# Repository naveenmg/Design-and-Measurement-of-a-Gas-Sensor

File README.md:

# Design and Measurement of a Gas Sensor

### Task

The aim of this project is to develop a semiconductor gas sensor to measure the concentration of methane. Metal oxide sensors are also known as chemiresistors. The detection principle of resistive sensors is based on the change of resistance of a thin film upon adsorption of the gas molecules on the surface of a semiconductor. The gas-solid interactions affect the resistance of the film because of the density of electronic species in the film.

Two substrates consisting of aluminum oxide (Al2O3) are given for this project. The development processes will be explained in the following chapters. It includes sputtering, design of the electrode structure, laser structuring, microscopy, design and layout of a printed circuit board (PCB), soldering and testing.

## Structure of the gas sensor

In order to be able to apply the principle of operation a pattern of conductors has to be created between two contact surfaces. These surfaces as well as the conductors consist of a thin layer of platinum which itself is on top of a non-conductive substrate. Above the platinum pattern there is a layer of tin oxide, but at the contacting surfaces the platinum is still exposed. In order to make the effect (change in resistance) easier to measure, the surface area of the pattern should be as high as possible. This is achieved by having small distances between the conductors in the pattern. Since the effect occurs mainly in the space charge zone, the reaction material should be applied only in a thin layer.

To implement the design of the electrodes, the Easily Applicable Graphical Layout Editor (EAGLE) was used. This software is suitable for creating schematics and layouts for board designs, but also includes other features.

## Sputtering
Sputtering is one possibility of physical vapor deposition (PVD) to create a thin layer on a substrate material. Sputtering is used, because of the good edge covering, flexibility of the sputtered materials and the low temperature stress. In this project, a combination of AC- and magnetron-sputtering is used to create a thin layer of platinum on the ceramic substrate.

## Laser Structuring
The aim of laser structuring is the targeted evaporation of the platinum layer on the ceramic plate at defined geometries.

## Measurement
First, the sensor was fixed on a rod and the rod was inserted into a glass tube. The glass tube was then put into the oven which was heated to 400°C. During the heating process of the sensor, the PCB was connected to the power supply and multimeters. 

While the sensor reached the operating temperature, the voltmeters were connected to the board for equipotential bonding and recording of the trace. The other pins on the board like the voltage source pins were also connected. The zero-point adjustment of the wheatstone bridge was performed by adjusting the potentiometer on the PCB with the help of a voltmeter. Thereafter, the gain of the instrumentation amplifier circuit was adjusted to a factor of about 10 with the aid of the measured output and input voltages. In order to record the sensor behavior with different gas compositions, the gas mixing plant was able to conduct differently composed gas mixtures into the gas flow heating tube with the sensor element. Figure 21 shows the control panel of the gas mixing plant. 

The gas mixing plant controls the gas flow into the glass tube. It had the following settings:  
Channel 1: Nitrogen N2: 0.8 slm 
Channel 2: Oxygen O2: 0.2 slm 
Channel 3: Methane CH4: 0.0 sccm 

Note: 1 slm (standard liter per minute) = 1000 sccm (standard cubic centimeter per minute)

Nitrogen and oxygen gases were always flowing through the glass tube in order to create a mixture similar to air, but without any impurities. Methane was turned on and off periodically in different concentrations to test the sensitivity of the sensor. After the sensor was placed into the oven it took about 10 minutes until a constant temperature of 400°C was reached. With that completed, the measurement could start by using a software which automatically saves and plots the measured values. When methane gas was turned on, the voltage decreased. The voltage returned to its previous state when methane gas was turned off.

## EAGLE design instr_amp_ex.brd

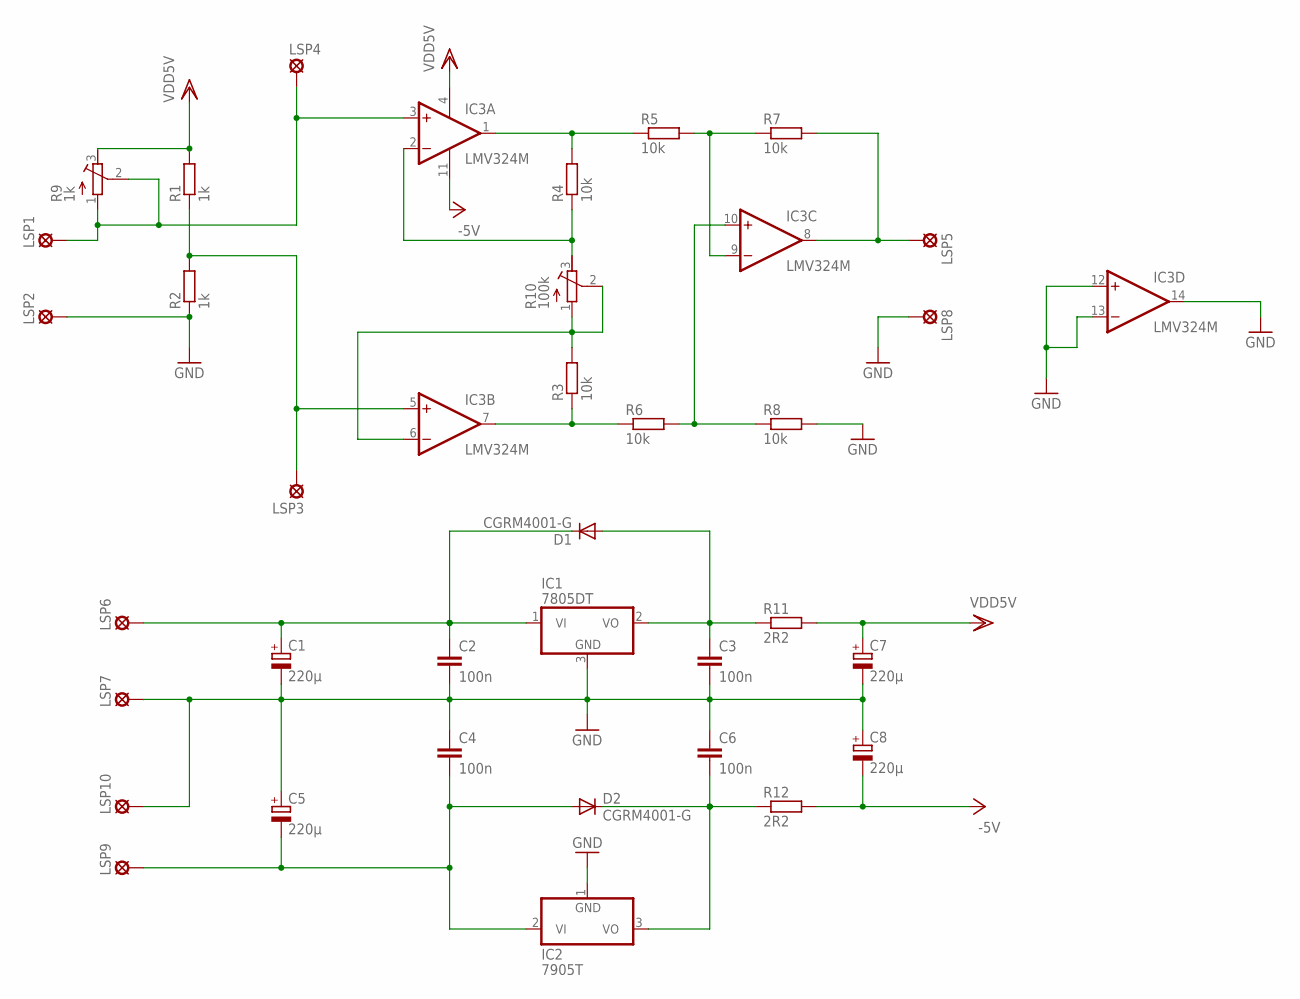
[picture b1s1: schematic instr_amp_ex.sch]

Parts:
C1, C5, C7, C8: 220µ; 085CS_1AW
C2, C3, C4, C6: 100n; C1206K
D1, D2: CGRM4001-G; SOD-123_MINI-SMA
IC1: 7805DT; TO252
IC2: 7905T; TO220H
IC3: LMV324M; SO14
LSP1, LSP2, LSP3, LSP4, LSP5, LSP6, LSP7, LSP8, LSP9, LSP10: LSP13
R1, R2: 1k; R1206
R3, R4, R5, R6, R7, R8: 10k; R1206
R9: 1k; RTRIM3224W
R10: 100k; RTRIM3224W
R11, R12: 2R2; R1206

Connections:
-5V: C8.-, IC3.11 (V-), R12.2
GND: C1.-, C2.2, C3.2, C4.1, C5.+, C6.1, C7.-, C8.+, IC1.3 (GND), IC2.1 (GND), IC3.12 (+IN), IC3.13 (-IN), IC3.14 (OUT), LSP2.MP, LSP7.MP, LSP8.MP, LSP10.MP, R2.1, R8.2
unnamed: IC3.5 (+IN), LSP3.MP, R1.1, R2.2
unnamed: C3.1, D1.A, IC1.2 (VO), R11.1
unnamed: IC3.3 (+IN), LSP1.MP, LSP4.MP, R9.1 (A), R9.2 (S)
unnamed: C6.2, D2.C, IC2.3 (VO), R12.1
unnamed: IC3.1 (OUT), R4.2, R5.1
unnamed: IC3.10 (+IN), R6.2, R8.1
unnamed: IC3.7 (OUT), R3.1, R6.1
unnamed: C1.+, C2.1, D1.C, IC1.1 (VI), LSP6.MP
unnamed: IC3.2 (-IN), R4.1, R10.3 (E)
unnamed: IC3.9 (-IN), R5.2, R7.1
unnamed: IC3.8 (OUT), LSP5.MP, R7.2
unnamed: IC3.6 (-IN), R3.2, R10.1 (A), R10.2 (S)
unnamed: C4.2, C5.-, D2.A, IC2.2 (VI), LSP9.MP
VDD: C7.+, IC3.4 (V+), R1.2, R9.3 (E), R11.2

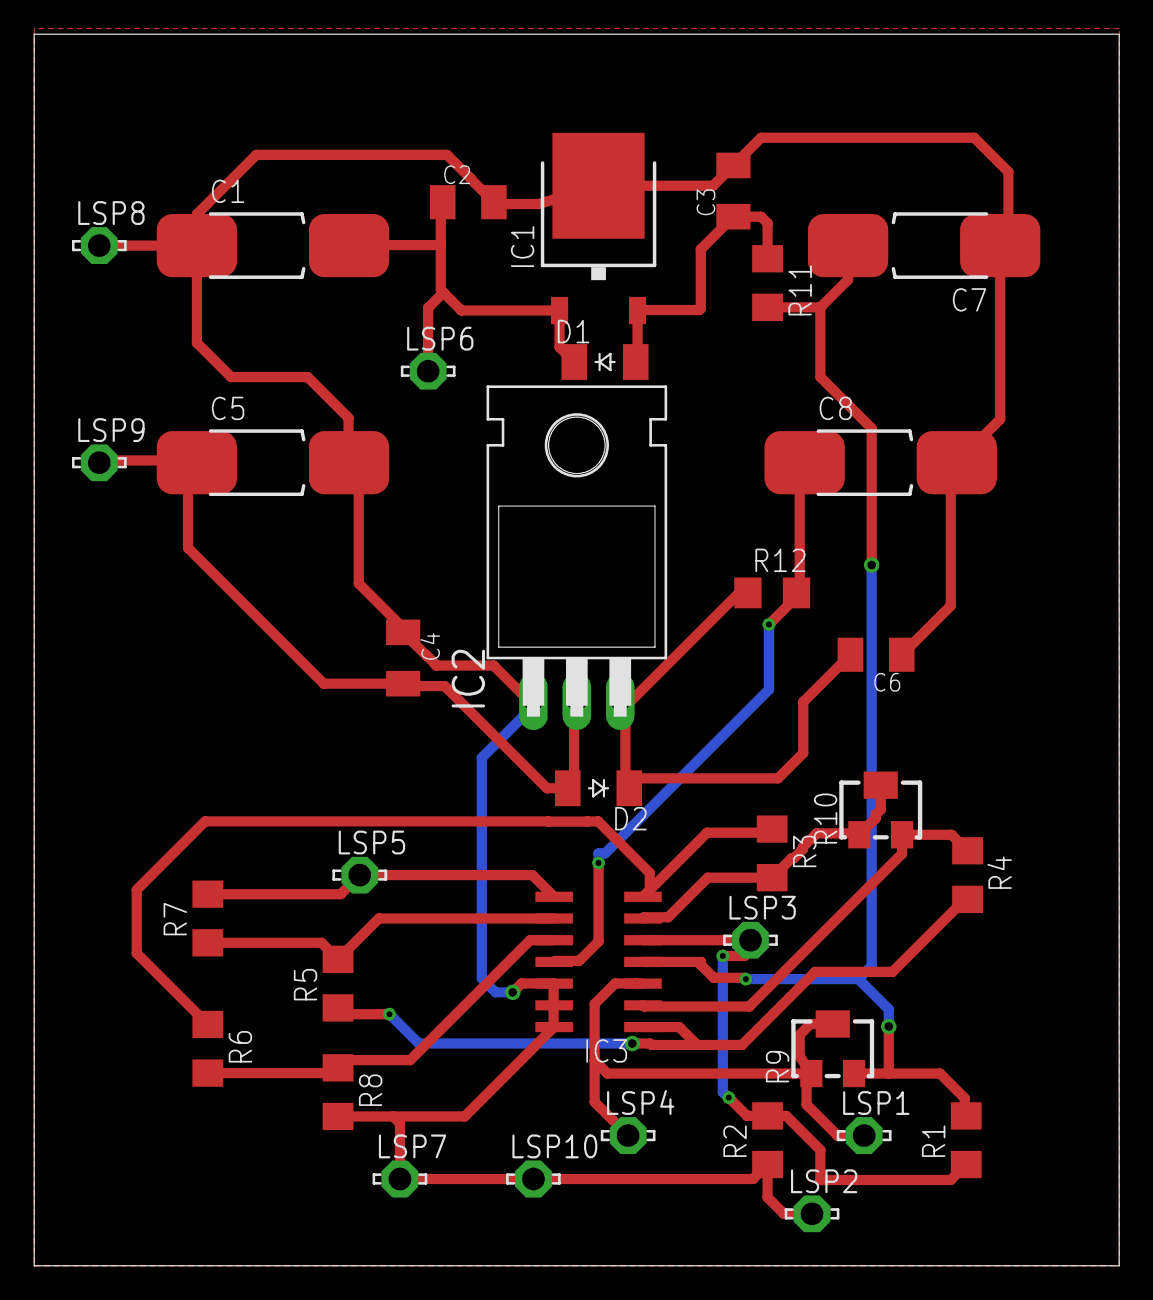
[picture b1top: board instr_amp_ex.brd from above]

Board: 2 copper layers, 63.5 x 72.1 mm, 35 parts (0 on the bottom side), 16 nets.
